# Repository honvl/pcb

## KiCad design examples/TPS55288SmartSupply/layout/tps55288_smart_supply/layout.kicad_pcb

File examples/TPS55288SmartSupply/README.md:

# TPS55288 Smart Supply

This example is a digitally controlled CC/CV bench-supply schematic built around `TPS55288`.

It is intended as a more honest replacement for a generic `LTC3780` module:
- power stage: `TPS55288RPMR`
- MCU: `STM32G0B1CBT6`
- telemetry: `INA226AIDGSR`
- 3.3 V logic rail: `AP2112K-3.3TRG1`
- user input: EC11 rotary encoder with push switch
- display: 4-pin header for a common I2C `SSD1306` OLED module
- input options:
  - 3.3V to 28V screw-terminal input for the main power path
  - USB-C PD/PPS input handled directly by the MCU's `UCPD` peripheral

## What the hardware supports

- Software-set output voltage over I2C through the TPS55288 internal feedback path
- Software-set output current limit over I2C
- USB-PD / PPS sink negotiation through the STM32 `UCPD` peripheral
- Independent output voltage and current measurement with INA226
- MCU-visible input sensing:
  - the screw-terminal input is divided down to a GPIO/ADC pin so firmware can detect main-input presence
- A single encoder that firmware can use as:
  - rotate to change the active setpoint
  - press to switch between voltage-set and current-set editing
- A manual source-select input path:
  - a single SPDT switch selects either the screw-terminal input or the USB-C PD/PPS input
  - this removes the expensive ideal-diode priority mux at the cost of automatic failover

## Notes

- This schematic does not include firmware.
- The OLED interface is a simple `GND / 3V3 / SCL / SDA` header instead of a fixed display module footprint.
- The TPS55288 power stage is based on TI's own reference schematic, but simplified for internal-feedback operation.
- The honest advertised input range is:
  - main screw-terminal input: `3.3V to 28V`
  - USB-C PD/PPS input: `5V to 20V`
- The practical continuous current target is about `5A` to `6A`, not the inflated `10A` headline used by many cheap modules.
- For routing constraints, treat the main power rails and switching path as a `6A` design target, not `8A`.
- Low input voltage reduces available output power sharply. The board can start around `3.3V`, but the widest output range and highest current are only realistic from higher input voltage.
- The USB-C input is a real PD/PPS path, but it is still capped by cable/source contracts and the `3A` USB fuse. The main screw-terminal input remains the better choice for heavy continuous loads.
- The USB connector is still the simple 6-pin power-only receptacle because PD/PPS only needs `VBUS`, `GND`, and the `CC` pins in this design.
- The input source is user-selected with a switch. Do not hot-switch sources under heavy load unless the chosen hardware is rated for it.
- `SWIN` is pinned to Dailywell `1MS1T1B1M1QES-5` because it is a cheap JLC-available SPDT toggle. It is only a `28VDC / 5A` part, so it does not fully cover the schematic's `8A` rail target.
- For Quilter, assume a `Top / GND / Signal / Bottom` 4-layer stackup, not `Top / GND / Power / Bottom`.
- Keep `L2` as a solid uninterrupted ground plane.
- Use `L3` for signal escape and small local copper pours only; do not dedicate it as a global power plane.
- Route `VIN_MAIN`, `VIN`, `VOUT_RAW`, and `VOUT` as short outer-layer pours near the power stage instead of trying to bury them in an inner-plane island.
- Keep `SW1` and `SW2` short and wide on the outer layers, but do not pour them.

## Sources

- TI TPS55288 datasheet: <https://www.ti.com/lit/ds/symlink/tps55288.pdf>
- ST STM32G0B1 datasheet: <https://www.st.com/resource/en/datasheet/stm32g0b1cb.pdf>
- TI TPS55288EVM-045 user guide: <https://www.ti.com/lit/pdf/SLVUBO4B>
- TI TPS55288 layout guideline: <https://www.ti.com/lit/an/slvaer0/slvaer0.pdf>

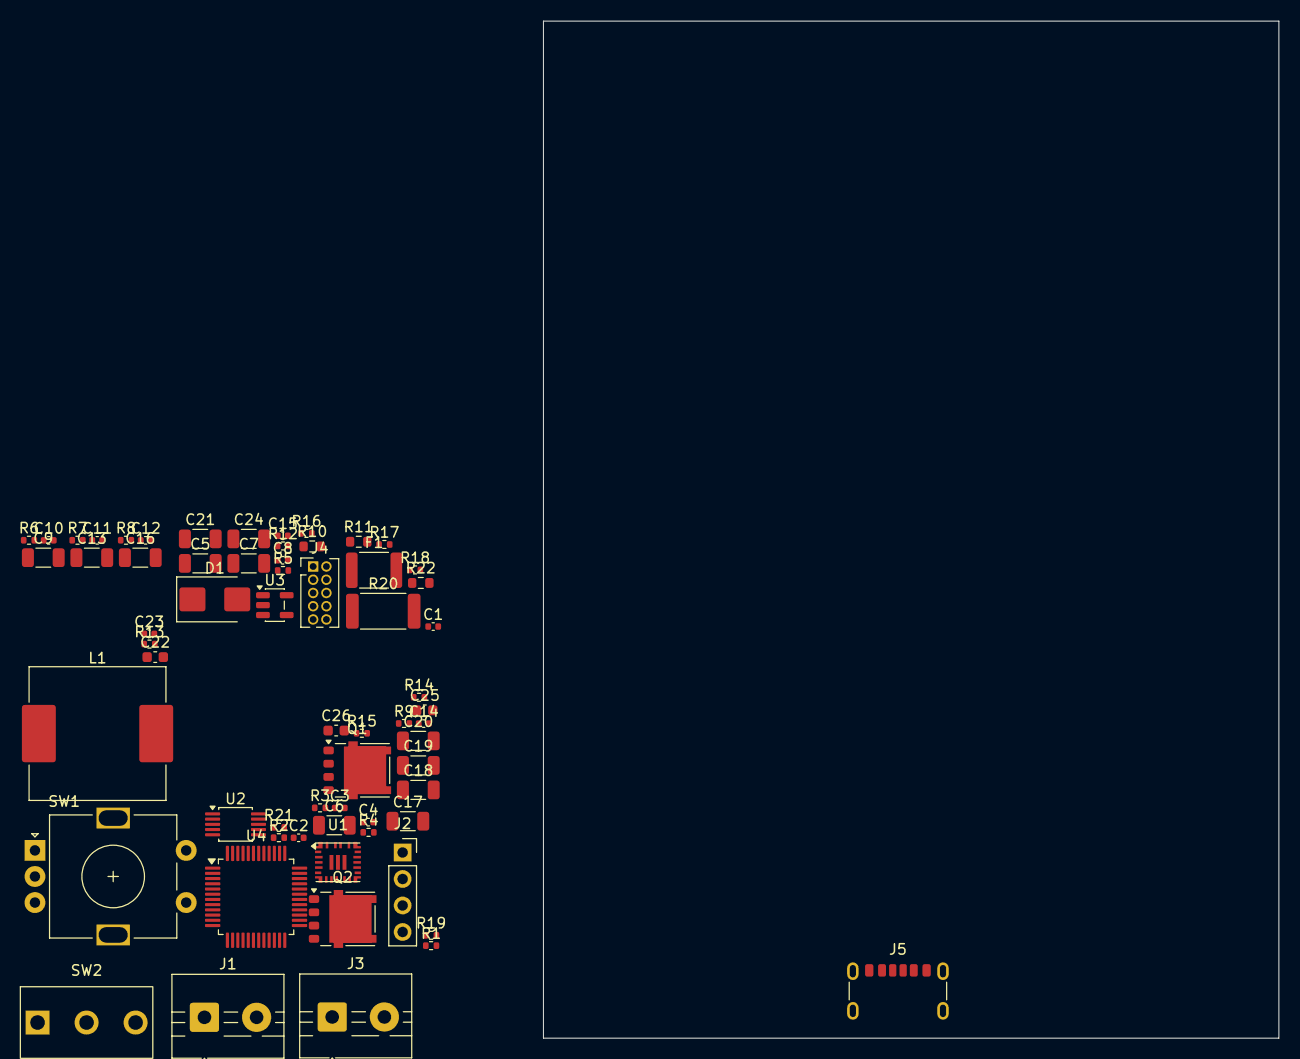
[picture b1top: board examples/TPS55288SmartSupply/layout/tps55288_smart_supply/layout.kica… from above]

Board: 4 copper layers, 70.5 x 97.5 mm, 64 parts (0 on the bottom side), 41 nets, no tracks yet.

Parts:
C1, C2, C8, C10, C15: GCM155R71H104KE02D; C_0402_1005Metric
C3: GCM1555C1H101FA16D; C_0402_1005Metric
C4: 0402B472K500NT; C_0402_1005Metric
C5, C6, C7, C9, C13, C20, C21, C24: CL31A106KBHNNNE; C_1206_3216Metric
C11, C12, C14: GRM155Z71A105KE01D; C_0402_1005Metric
C16, C17, C18, C19: GRT31CR61H106KE01K; C_1206_3216Metric
C22, C26: CL10A105KB8NNNC; C_0603_1608Metric
C23: GRM1555CYA103GE01D; C_0402_1005Metric
C25: GRM188Z71C475KE21D; C_0603_1608Metric
D1: SMBJ24A; D_SMB
F1: 1812L300/30GR; Fuse_1812_4532Metric
J1, J3: 282836-2; TerminalBlock_MaiXu_MX126-5.0-02P_1x02_P5.00mm
J2: 2.54mm 4 x 1 THT Vertical Female; PinSocket_1x04_P2.54mm_Vertical
J4: 62201021121; PinHeader_2x05_P1.27mm_Vertical
J5: USB4125-GF-A; USB_C_Receptacle_GCT_USB4125-xx-x-0190_6P_TopMnt_Horizontal
L1: VCMA-1365-4R7-M-1A; L_Changjiang_FXL1360
Q1, Q2: NTMFS5C628NLT1G; ONSemi_SO-8FL_488AA
R1: ERJ-2RKF5622X; R_0402_1005Metric
R2, R3, R18: ERJ-2GE0R00X; R_0402_1005Metric
R4, R5, R6, R15, R19: ERJ-2RKF1002X; R_0402_1005Metric
R7, R8: ERJ-H2CF10R0X; R_0402_1005Metric
R9: ERJ-2RKF4992X; R_0402_1005Metric
R10, R11: ERJ-H3QF1R0V; R_0603_1608Metric
R12, R13: ERJ-2RKF2201X; R_0402_1005Metric
R14: ERJ-2RKF2002X; R_0402_1005Metric
R16, R17: ERJ-2RKF1003X; R_0402_1005Metric
R20: PA2512FKF7T0R005E; R_2512_6332Metric
R21: ERJ-2RKF1153X; R_0402_1005Metric
R22: ERJ-3EKF1963V; R_0603_1608Metric
SW1: EC11N1525404; RotaryEncoder_Alps_EC11E-Switch_Vertical_H20mm
SW2: 1MS1T1B1M1QES-5; SW_Toggle_SPDT_Dailywell_1MS1T1B1M1QES-5
U1: TPS55288RPMR
U2: INA226AIDGSR; VSSOP-10_3x3mm_P0.5mm
U3: AP2112K-3.3TRG1; SOT-23-5
U4: STM32G0B1CBT6; LQFP-48_7x7mm_P0.5mm

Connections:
BOOT1: C1.1, U1.22
BOOT2: C2.1, U1.20
COMP: C3.1, R1.1, U1.18
COMP_RC: C3.2, C4.1, R1.2
DITH_SYNC: C23.1, U1.7, U1.28
DRIVE_H: R10.1, U1.2
DRIVE_L: R11.1, U1.1, U1.27
ENC_A: R4.2, SW1.A, U4.11
ENC_B: R5.2, SW1.B, U4.12
ENC_SW: R6.2, SW1.S1, U4.13
EN_UVLO: R21.1, R22.2, U1.4
FSW_CFG: R9.1, U1.8
GND: C4.2, C5.2, C6.2, C7.2, C8.2, C9.2, C11.2, C12.2, C13.2, C14.2, C15.2, C16.2, C17.2, C18.2, C19.2, C20.2, C21.2, C22.2, C23.2, C24.2, C25.2, C26.2, D1.1, J1.2, J2.1, J3.2, J4.3, J4.5, J4.9, J5.A12, J5.B12, J5.S1, Q2.1, Q2.2, Q2.3, R9.2, R14.2, R16.2, R18.2, R21.2, SW1.C, SW1.MP, SW1.S2, U1.9, U1.10, U1.24, U2.1, U2.2, U2.7, U3.2, U4.7
I2C_CTRL_SCL: J2.3, R12.2, U1.5, U2.5, U4.47
I2C_CTRL_SDA: J2.4, R13.2, U1.6, U2.4, U4.48
ILIM_CFG: R14.1, U1.17
INA_ALERT_N: R15.2, U2.3, U4.14
ISENSE_N: C10.2, R7.2, U2.9
ISENSE_P: C10.1, R8.2, U2.10
MAIN_PRESENT: R16.1, R17.2, U4.17
MODE_CFG: R18.1, U1.15
NRST: J4.10, R19.2, U4.10
Q1_GATE: Q1.4, R10.2
Q2_GATE: Q2.4, R11.2
SW1: C1.2, L1.1, Q1.1, Q1.2, Q1.3, Q2.5, U1.23
SW2: C2.2, L1.2, U1.21, U1.25
SWCLK: J4.4, U4.36
SWDIO: J4.2, U4.35
SWO: J4.6, U4.42
USB_CC1: J5.A5, R2.1, U4.28
USB_CC2: J5.B5, R3.1, U4.27
USB_DBCC1: R2.2, U4.29
USB_DBCC2: R3.2, U4.32
VCC_5V: C11.1, C25.1, U1.19, U1.30, U3.1, U3.3
VDD_3V3: C8.1, C12.1, C14.1, C15.1, J2.2, J4.1, R4.1, R5.1, R6.1, R12.1, R13.1, R15.1, R19.1, U2.6, U3.5, U4.4, U4.5, U4.6
VIN: C5.1, C6.1, C7.1, C9.1, C26.1, Q1.5, R22.1, SW2.2, U1.3
VIN_MAIN: C13.1, J1.1, R17.1, SW2.1
VIN_USB: F1.1, J5.A9, J5.B9
VIN_USB_FUSED: C24.1, D1.2, F1.2, SW2.3
VOUT: C22.1, J3.1, R7.1, R20.2, U1.13, U1.29
VOUT_RAW: C16.1, C17.1, C18.1, C19.1, C20.1, C21.1, R8.1, R20.1, U1.11, U1.12, U1.26, U2.8

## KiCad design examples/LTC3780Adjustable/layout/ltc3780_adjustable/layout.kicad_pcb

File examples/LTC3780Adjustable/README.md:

# LTC3780 Adjustable Buck Example

This example adapts the official LTC3780 reference design to a buck-only use case:

- `VIN = 5V`
- `VOUT ≈ 3.3V adjustable`
- `IOUT target = 10A`

## Reference Sources

- LTC3780 datasheet: <https://www.analog.com/media/en/technical-documentation/data-sheets/ltc3780.pdf>
- DC686A evaluation board: <https://www.analog.com/en/resources/evaluation-hardware-and-software/evaluation-boards-kits/dc686a.html>
- DC686A schematic: <https://www.analog.com/media/en/technical-documentation/eval-board-schematic/686asch.pdf>

## Output Adjust Range

The feedback divider is:

- `RFB_BOTTOM = 10k`
- `RFB_FIXED = 26.1k`
- `RV1 = 0k..10k` wired as a rheostat

Using `VOUT = 0.8V * (1 + RTOP / RBOTTOM)`:

- minimum `VOUT ≈ 2.89V`
- maximum `VOUT ≈ 3.69V`
- nominal near mid-trim `VOUT ≈ 3.29V`

## Notes

- `FCB` is tied low for forced-continuous operation.
- `PLLFLTR` is tied low and `PLLIN` is left open, so the converter runs at the minimum internal frequency of about `200kHz`.
- `EXTVCC` is left open because this design stays below the `5.7V` switchover threshold.
- The power stage now uses concrete, JLC-checkable parts and footprints: `NTMFS5C670NLT1G` MOSFETs in KiCad's `ONSemi_SO-8FL_488AA`, `XAL7070-472MEC` on a local KiCad footprint generated from ComponentSearchEngine data, and a fully specified ceramic input/output capacitor bank built around `GRM32ER71A476KE15L`.
- The compensation network and local decoupling caps are also tied to real Murata and Panasonic parts, including `GRM1555C1H222GA01D` for `CITH` and `PA2512FKF7W0R01E` for `RSENSE`.
- `COUT4` was changed from a polymer placeholder to a fourth `47uF` MLCC so the example stays within exact, library-backed footprints.
- PCBparts/JLC results materially changed selection: `LTC3780EG#PBF`, `PA2512FKF7W0R01E`, `B340A-13-F`, `TC33X-2-103E`, and the Murata caps are stocked; the original `Si7884DP-T1-GE3` was not found in JLC and the original `XAL7030-472MEC` was only rated `9A`, so both were replaced.
- Compensation, thermal margin, inductor saturation, capacitor bias derating, and transient response still need validation on hardware.

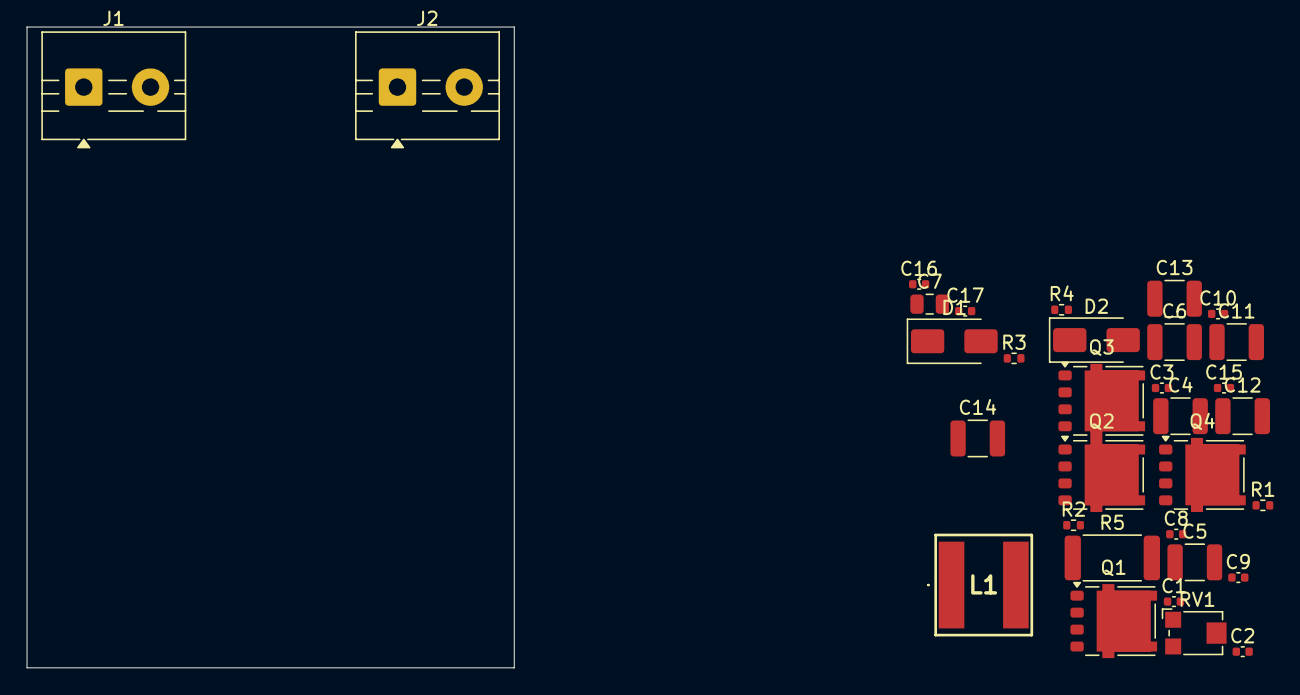
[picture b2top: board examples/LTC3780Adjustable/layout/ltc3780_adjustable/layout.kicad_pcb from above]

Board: 4 copper layers, 36.5 x 48.0 mm, 32 parts (0 on the bottom side), 11 nets, no tracks yet.

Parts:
C1, C2, C9, C15, C17: GCM155R71H104KE02D; C_0402_1005Metric
C3: GCM1555C1H470FA16D; C_0402_1005Metric
C4, C5, C6, C11, C12, C13, C14: GRM32ER71A476KE15L; C_1210_3225Metric
C7: GRM21BR71C475KE51L; C_0805_2012Metric
C8: GRM155Z71A105KE01D; C_0402_1005Metric
C10: GRM1555C1H222GA01D; C_0402_1005Metric
C16: GCM155R71H223KA55D; C_0402_1005Metric
D1, D2: B340A-13-F; D_SMA
J1, J2: 282836-2; TerminalBlock_MaiXu_MX126-5.0-02P_1x02_P5.00mm
L1: XAL7070-472MEC; XAL7070472MEC
Q1, Q2, Q3, Q4: NTMFS5C670NLT1G; ONSemi_SO-8FL_488AA
R1: ERJ-2RKF1002X; R_0402_1005Metric
R2: ERJ-2RKF2612X; R_0402_1005Metric
R3: ERJ-2RKF2002X; R_0402_1005Metric
R4: ERJ-2RKF1003X; R_0402_1005Metric
R5: PA2512FKF7W0R01E; R_2512_6332Metric
RV1: TC33X-2-103E; Potentiometer_Bourns_TC33X_Vertical

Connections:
CS: C7.2, C8.2, D1.2, Q2.1, Q2.2, Q2.3, Q3.1, Q3.2, Q3.3, R5.1
GND: C4.2, C5.2, C6.2, C9.2, C10.2, C11.2, C12.2, C13.2, C14.2, C15.2, C16.2, C17.2, J1.2, J2.2, R1.2, R5.2
INTVCC: C7.1, C8.1
ITH: C15.1, R3.1
ITH_RC: C10.1, R3.2
SW1: C1.2, D1.1, L1.1, Q1.1, Q1.2, Q1.3, Q2.5
SW2: C2.2, D2.2, L1.2, Q3.5, Q4.1, Q4.2, Q4.3
VFB: C3.2, R1.1, RV1.2, RV1.3
VFB_TOP: R2.2, RV1.1
VIN_5V: C4.1, C5.1, C6.1, C9.1, J1.1, Q1.5, R4.2
VOUT_ADJ: C3.1, C11.1, C12.1, C13.1, C14.1, D2.1, J2.1, Q4.5, R2.1

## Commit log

2026-04-25 Add power supply examples
